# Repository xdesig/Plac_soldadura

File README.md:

#  Plataforma de Soldadura (Control de Temperatura)

> [!NOTE]
> Documentation in Galego 
> [traductor](https://tradutorgaio.xunta.gal/TradutorPublico/traducir/index)

Este repositorio conten o deseno de hardware, esquema e firmware para o desenvolvemento dun **controlador termico intelixente** aplicado a unha placa calefactora de 230Vac. O sistema esta desenado para labores de soldadura e desoldadura de componentes SMD/THD en proxectos persoais, educativos e experimentais.

---

## Versions do Proxecto

O repositorio esta dividido en duas variantes segundo o microcontrolador utilizado:

### 1. [Plataforma_sold_ATmega328p](./Plataforma_sold_ATmega328p)

- **Microcontrolador:** ATmega328P-AU (TQFP-32).
- **Descricion:** Version mais lixeira e eficiente baseada na arquitectura clasica de Arduino. Demostra que non e preciso usar un potente ESP32 para realizar este traballo.
**Caracteristicas:** Control de potencia, visualizacion en pantalla OLED 128x64 (SSD1306) e illamento galvanico.

**[Ver documentacion e BOM do ATmega328P](./Plataforma_sold_ATmega328p)**

---

### 2. [Plataforma_sold_ESP32-C3](./Plataforma_sold_ESP32-C3)

**Microcontrolador:** ESP32-C3 SuperMini (RISC-V).
**Descricion:** Version baseada no chip ESP32-C3, aproveitando a sua maior velocidade de procesamento e conectividade.
**Caracteristicas:** Interface OLED I2C, control mediante encoder rotatorio e procesamento mais rapido da curva de temperatura.

**[Ver documentacion e BOM do ESP32-C3](./Plataforma_sold_ESP32-C3)**

---

##  Caracteristicas Xerais

Ambas versions comparten a seguinte arquitectura e funcionalidade basica:

- **Control Termico:** Axuste preciso da temperatura e control de potencia do elemento calefactor.
- **Seguridade:** Deteccion de fallos no termistor e corte de emerxencia por sobrequecemento (300 C).
- **Aisllamento:** Illamento galvanico mediante micro-fonte de alimentacion conmutada integrada na PCB.
- **Etapa de Potencia:** Control de carga AC a 230Vac mediante SSR / Triac (BTA06-400B e optoacoplador MOC3041).
- **Interface:** Pantalla OLED SSD1306 (128x64 px) e selector mediante encoder rotatorio e pulsador.

---

## Estrutura do Repositorio

* `Plataforma_sold_ATmega328p/`: Proxecto, PCB e BOM para ATmega328P
* `Plataforma_sold_ESP32-C3/`: Proxecto, PCB e BOM para ESP32-C3
* `README.md`: Descricion xeral do repositorio

---

Saúdos.

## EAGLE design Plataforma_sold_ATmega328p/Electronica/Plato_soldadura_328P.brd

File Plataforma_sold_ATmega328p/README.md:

# Controlador de placa para soldar Con ATmega328p

> [!NOTE]
> Documentation in Galego 
> [traductor](https://tradutorgaio.xunta.gal/TradutorPublico/traducir/index)

Tr&aacute;tase dun **controlador t&eacute;rmico intelixente** de placa calefactora 230Vac para soldar/desoldar, dese&ntilde;ado para uso persoal, educativo e experimental. Baseado en ATmega328, non &eacute; preciso usar un potente ESP32 para realizar este traballo, e permite:

- Axuste preciso da temperatura (ata 300&deg;C).
- Control "PID" simple e estable.
- Detecci&oacute;n de fallos do termistor.
- Gr&aacute;fico en tempo real da temperatura.
- Indicador ON/OFF e potencia aplicada ao calefactor na pantalla.
- Corte de emerxencia por sobrequecemento (300&deg;C).
- Illamento galv&aacute;nico (micro-fonte de alimentaci&oacute;n conmutada).
- Control mediante SSR (Triac) a 230Vac.

<br>
---

## [Versi&oacute;n 00]

## Listado de Compoñentes (BOM)

|Cant | Valor        | Dispositivo                       | Parte            | Descrición         |
|-----|--------------|-----------------------------------|------------------|------------------|
| **1** | 100R | R0603 | `R1` | Resistor |
| **1** | 100nF | C0603 | `C3` | Capacitor |
| **3** | 10K | R0603 | `R6`, `R8`, `R9` | Resistor |
| **1** | 10nF / 400V | C075-042X103 | `C1` | Capacitor (400V) |
| **1** | 10uF | C1206 | `C2` | Capacitor |
| **1** | 1K | R0603 | `R7` | Resistor |
| **1** | 1uF | C0603 | `C4` | Capacitor |
| **4** | 200R | R1206 | `R2`, `R3`, `R12`, `R13` | Resistor |
| **1** | 22-05-7028-02 | 7395-02 | `J1` | Connector |
| **1** | 39R | 0204/7 | `R4` | Resistor |
| **1** | 47K | R0603 | `R5` | Resistor |
| **2** | 4K7 | R0603 | `R10`, `R11` | Resistor |
| **1** | ATMEGA328P-AU | TQFP-32 | `IC3` | 8-bit Microcontrolador 32KB Flash |
| **1** | B3U-1000P | SMD_157SW | `S6` | Pulsador 4x3mm SMD H2.5mm |
| **1** | BTA06-400B (BT136) | TO-220AB | `T1` | Triac  |
| **1** | CSTCE16M0V53C-R0 | Resonador | `Y1` | Resonador 16MHz SMD |
| **1** | OLED 0.96" I2C | 128x64 Modulo | `OL1` | SSD1306 [GND, VCC, SCL, SDA] |
| **1** | Fusible| TE5 | `F1` | Fusible |
| **1** | MOC3041 | DIL06 / DIP-6 | `OK1` | Optoacoplador, Triac |
| **1** | Rotary Encoder | Rotary Enc Plain | `SW2` | Encoder rotativo pulsador |
| **1** | RPDZN5W6H | Module | `U1` | Modulo Micro fuente A. |

## Deseñado en Entrimo con agarimo.

### Author and license
* Author: XDeSIG [No Twitter, no X]
* License:[ CERN Open Hardware Licence Version 2 - S - Reciprocal][CERN-OHL-W]
* Certification:[ Open Hardware Certification: ES000057][OSHWA]

<br>

Sa&uacute;dos.
---
[ROTARTY_ENCODER]: https://github.com/xdesig/Plac_soldadura/blob/main/Imaxes/Rotary_encoder.webp
[RPDZN5W6H]: https://github.com/xdesig/Plac_soldadura/blob/main/Imaxes/ac-dc_5V700mA.png
[CERN-OHL-W]: https://ohwr.org/cern_ohl_w_v2.pdf
[OSHWA]: https://certification.oshwa.org/list.html

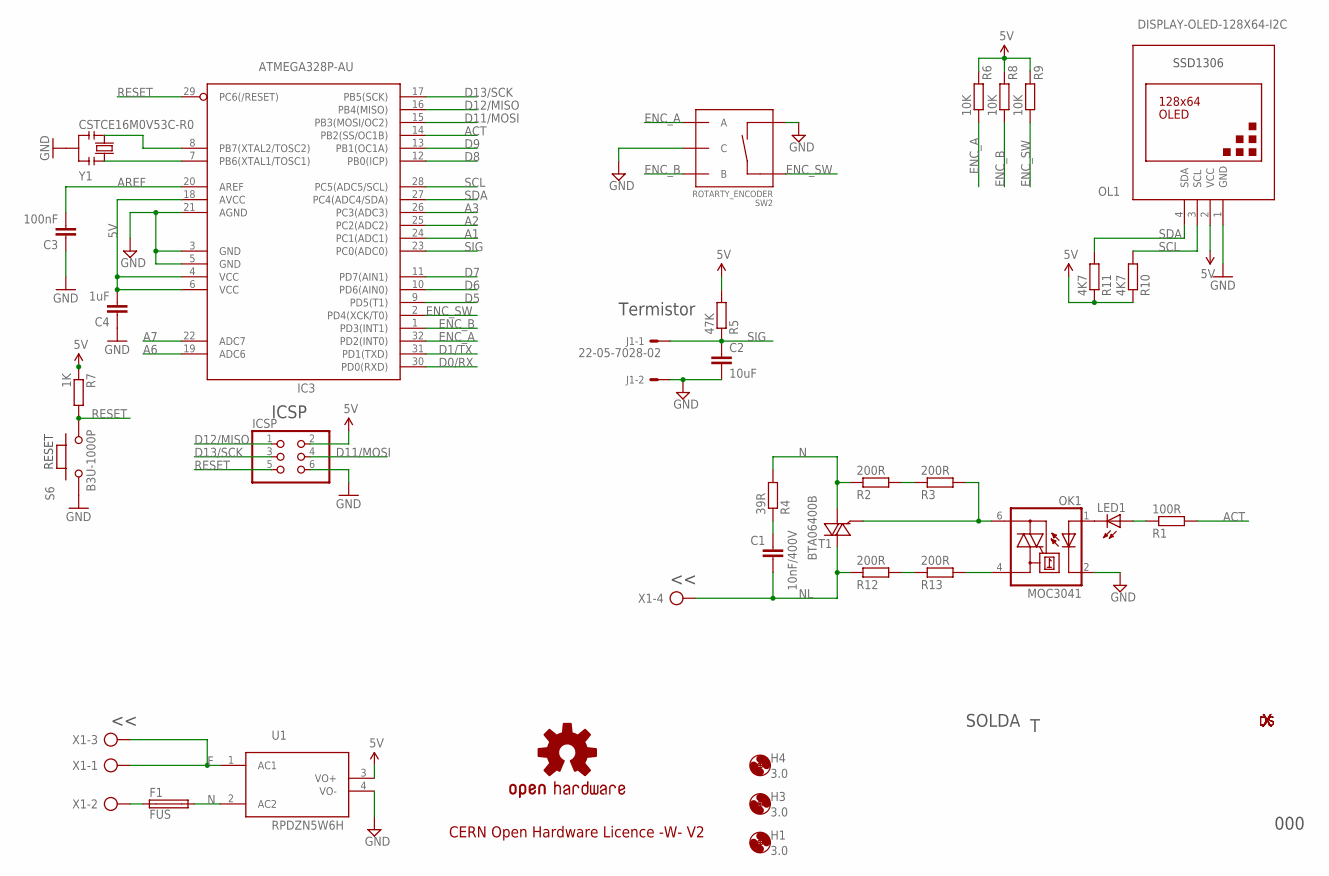
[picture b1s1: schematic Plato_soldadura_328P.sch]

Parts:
C1: 10nF/400V; C075-042X103
C2: 10uF; C1206
C3: 100nF; C0603
C4: 1uF; C0603
F1: FUS; TE5
H1, H3, H4: 3.0; 3,0
IC3: ATMEGA328P-AU; TQFP32-08
ICSP: 0114_PH254-203DF118A00V; 2X03
J1: 22-05-7028-02; 7395-02
LED1: LEDCHIP-LED0603; CHIP-LED0603
LOGO2: OSHW-LOGOL; ESCORNA_LBRESCORNA_CPU_2_10_SPARKFUN-AESTHETICS_OSHW-LOGO-L
OK1: MOC3041; DIL06
OL1: DISPLAY-OLED-128X64-I2C
R1: 100R; R0603
R2, R3, R12, R13: 200R; R1206
R4: 39R; 0204/7
R5: 47K; R0603
R6, R8, R9: 10K; R0603
R7: 1K; R0603
R10, R11: 4K7; R0603
S6: B3U-1000P; SMD_157SW
SW2: ROTARTY_ENCODER; ROTARY_ENC_PLAIN
T1: BTA06400B; TO220AB
U1: RPDZN5W6H
U$7: XDESIG_XDESIG5MM; XDESIG_XDESIG_CU
U$8: XDESIG_XDESIG21; XDESIG_XDESIG
X1: AK500/4-H
Y1: CSTCE16M0V53C-R0; RESONATOR

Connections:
5V: C4.2, IC3.4 (VCC), IC3.6 (VCC), IC3.18 (AVCC), ICSP.2, OL1.2 (VCC), R5.2, R6.2, R7.1, R8.2, R9.2, R10.1, R11.1, U1.3 (VO+)
A1: IC3.24 (PC1(ADC1))
A2: IC3.25 (PC2(ADC2))
A3: IC3.26 (PC3(ADC3))
A6: IC3.19 (ADC6)
A7: IC3.22 (ADC7)
ACT: IC3.14 (PB2(SS/OC1B)), R1.2
AREF: C3.2, IC3.20 (AREF)
D0/RX: IC3.30 (PD0(RXD))
D1/TX: IC3.31 (PD1(TXD))
D5: IC3.9 (PD5(T1))
D6: IC3.10 (PD6(AIN0))
D7: IC3.11 (PD7(AIN1))
D8: IC3.12 (PB0(ICP))
D9: IC3.13 (PB1(OC1A))
D11/MOSI: IC3.15 (PB3(MOSI/OC2)), ICSP.4
D12/MISO: IC3.16 (PB4(MISO)), ICSP.1
D13/SCK: IC3.17 (PB5(SCK)), ICSP.3
ENC_A: IC3.32 (PD2(INT0)), R6.1, SW2.A
ENC_B: IC3.1 (PD3(INT1)), R8.1, SW2.B
ENC_SW: IC3.2 (PD4(XCK/T0)), R9.1, SW2.SW+
F: U1.1 (AC1), X1.1, X1.3
GND: C2.2, C3.1, C4.1, IC3.3 (GND), IC3.5 (GND), IC3.21 (AGND), ICSP.6, J1.2, OK1.2 (C), OL1.1 (GND), S6.1, SW2.C, SW2.SW-, U1.4 (VO-), Y1.2
N: F1.2, R2.1, R4.2, T1.1 (A1), U1.2 (AC2)
unnamed: OK1.4 (A1), R13.2
unnamed: F1.1, X1.2
unnamed: OK1.6 (A2), R3.2, T1.3 (G)
unnamed: LED1.C, OK1.1 (A)
unnamed: LED1.A, R1.1
unnamed: R2.2, R3.1
unnamed: R12.2, R13.1
unnamed: C1.1, R4.1
unnamed: IC3.7 (PB6(XTAL1/TOSC1)), Y1.1
unnamed: IC3.8 (PB7(XTAL2/TOSC2)), Y1.3
NL: C1.2, R12.1, T1.2 (A2), X1.4
RESET: IC3.29 (PC6(/RESET)), ICSP.5, R7.2, S6.2
SCL: IC3.28 (PC5(ADC5/SCL)), OL1.3 (SCL), R10.2
SDA: IC3.27 (PC4(ADC4/SDA)), OL1.4 (SDA), R11.2
SIG: C2.1, IC3.23 (PC0(ADC0)), J1.1, R5.1

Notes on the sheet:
CERN Open Hardware Licence -W- V2
ICSP
RESET
Termistor
SOLDA
SSD1306
000

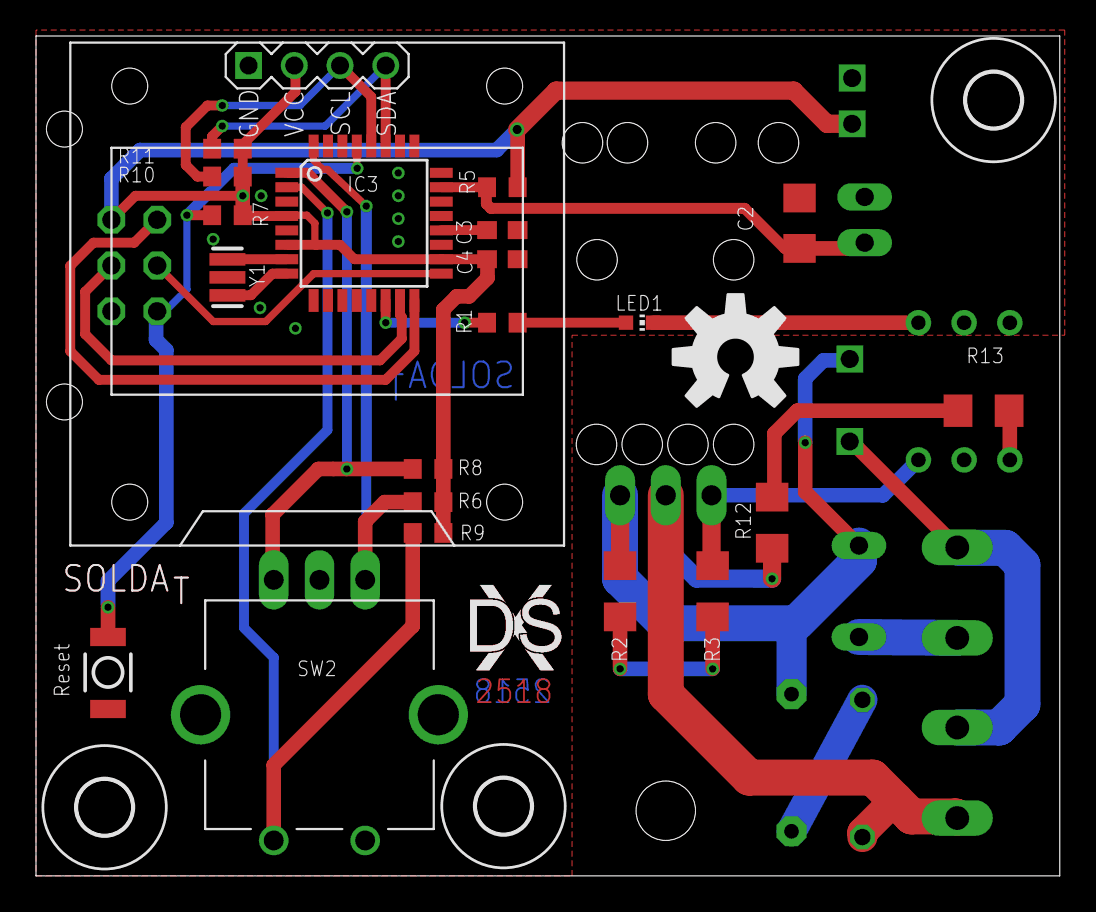
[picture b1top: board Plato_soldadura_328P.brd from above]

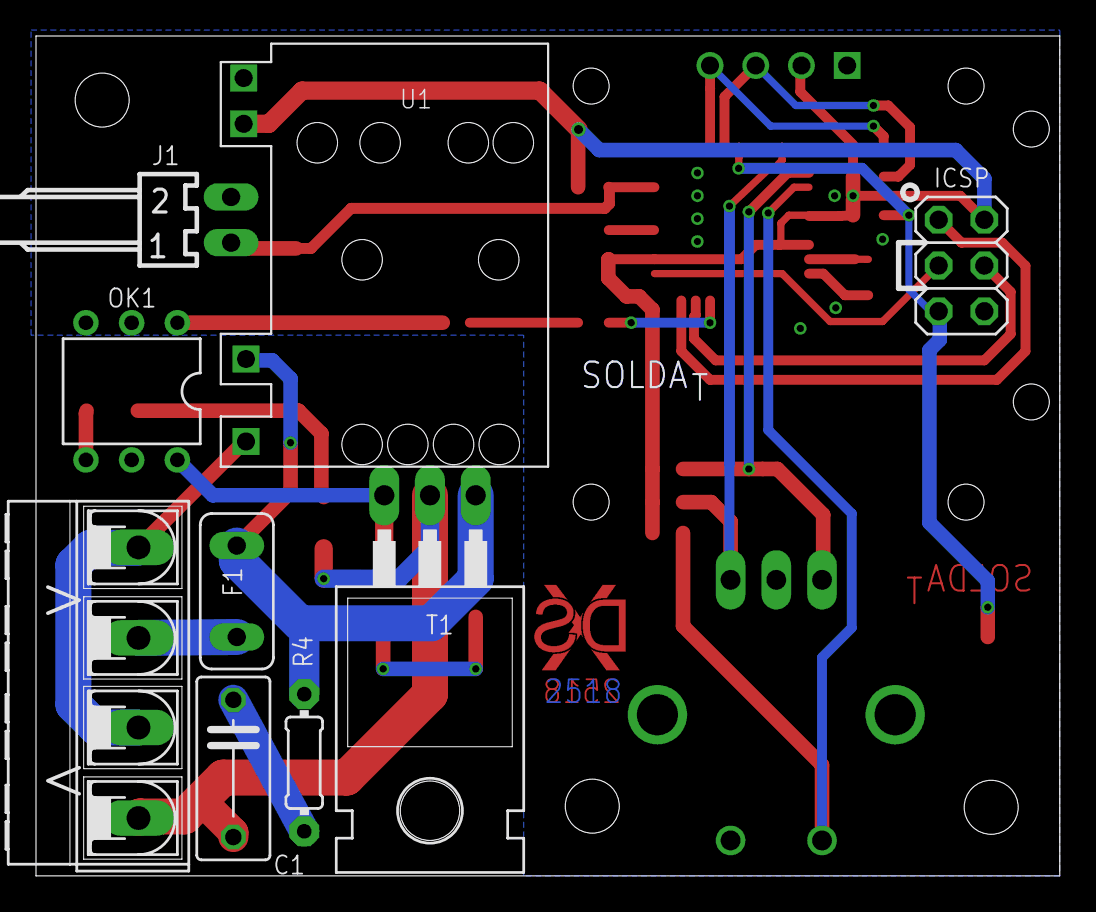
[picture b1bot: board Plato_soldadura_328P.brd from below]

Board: 2 copper layers, 56.9 x 46.7 mm, 36 parts (9 on the bottom side), 27 nets.

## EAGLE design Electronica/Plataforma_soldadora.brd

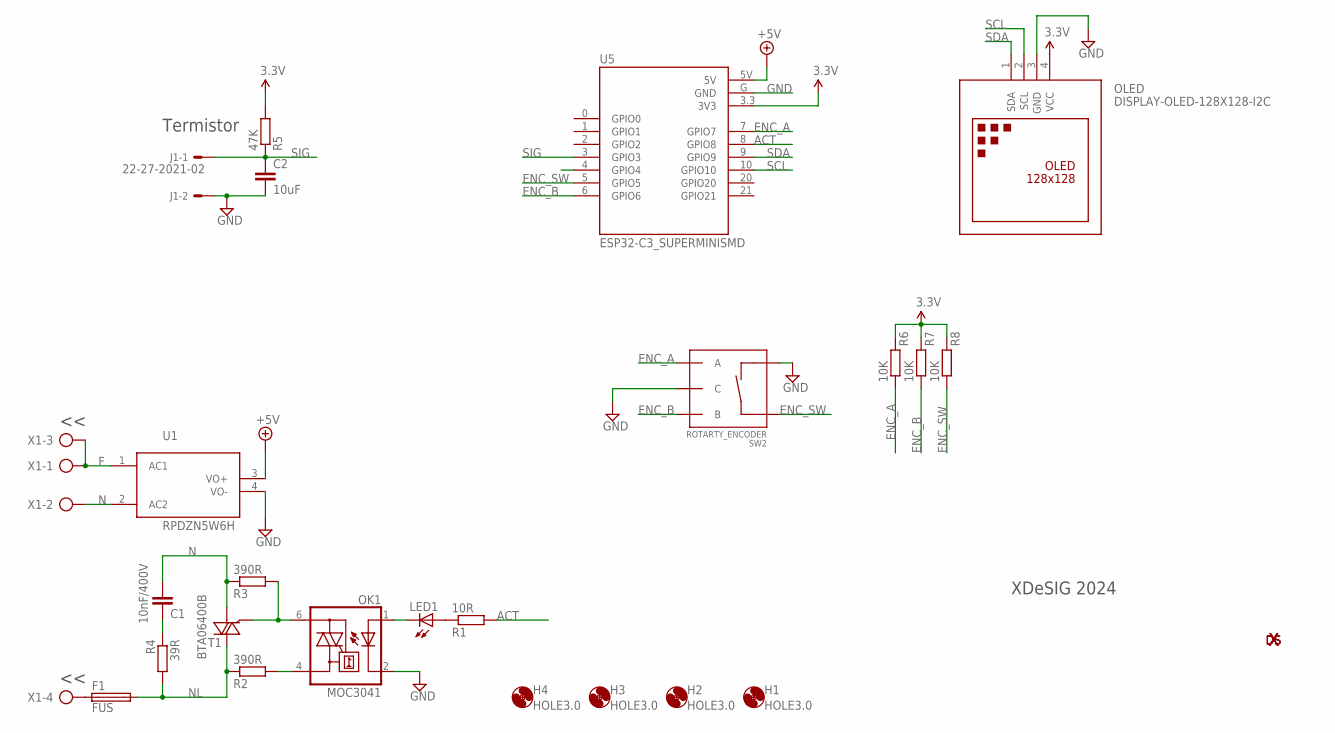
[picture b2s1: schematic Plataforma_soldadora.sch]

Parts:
C1: 10nF/400V; C075-042X103
C2: 10uF; C1206K
F1: FUS; TE5
H1, H2, H3, H4: HOLE3.0; HOLES_3,0
J1: 22-27-2021-02; 6410-02
LED1: LED3MM
OK1: MOC3041; DIL06
OLED: DISPLAY-OLED-128X128-I2C
R1: 10R; R0603
R2, R3: 390R; 0204/7
R4: 39R; 0204/7
R5: 47K; R0603
R6, R7, R8: 10K; R0603
SW2: ROTARTY_ENCODER; ROTARY_ENC_PLAIN
T1: BTA06400B; TO220AB
U1: RPDZN5W6H
U5: ESP32-C3_SUPERMINISMD; MODULE_ESP-C3_SUPERMINI_SMD
U$2: XDESIG_XDESIG5MM; XDESIG_XDESIG_CU
U$3: XDESIG_XDESIG21; XDESIG_XDESIG
X1: AK500/4-H

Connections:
3.3V: OLED.4 (VCC), R5.2, R6.2, R7.2, R8.2, U5.3.3 (3V3)
+5V: U1.3 (VO+), U5.5V
ACT: R1.2, U5.8 (GPIO8)
ENC_A: R6.1, SW2.A, U5.7 (GPIO7)
ENC_B: R7.1, SW2.B, U5.6 (GPIO6)
ENC_SW: R8.1, SW2.SW+, U5.5 (GPIO5)
F: U1.1 (AC1), X1.1, X1.3
GND: C2.2, J1.2, OK1.2 (C), OLED.3 (GND), SW2.C, SW2.SW-, U1.4 (VO-), U5.G (GND)
N: C1.2, R3.1, T1.1 (A1), U1.2 (AC2), X1.2
unnamed: OK1.4 (A1), R2.2
unnamed: F1.1, X1.4
unnamed: OK1.6 (A2), R3.2, T1.3 (G)
unnamed: LED1.K (C), OK1.1 (A)
unnamed: LED1.A, R1.1
unnamed: C1.1, R4.1
NL: F1.2, R2.1, R4.2, T1.2 (A2)
SCL: OLED.2 (SCL), U5.10 (GPIO10)
SDA: OLED.1 (SDA), U5.9 (GPIO9)
SIG: C2.1, J1.1, R5.1, U5.3 (GPIO3)

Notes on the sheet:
Termistor
XDeSIG 2024

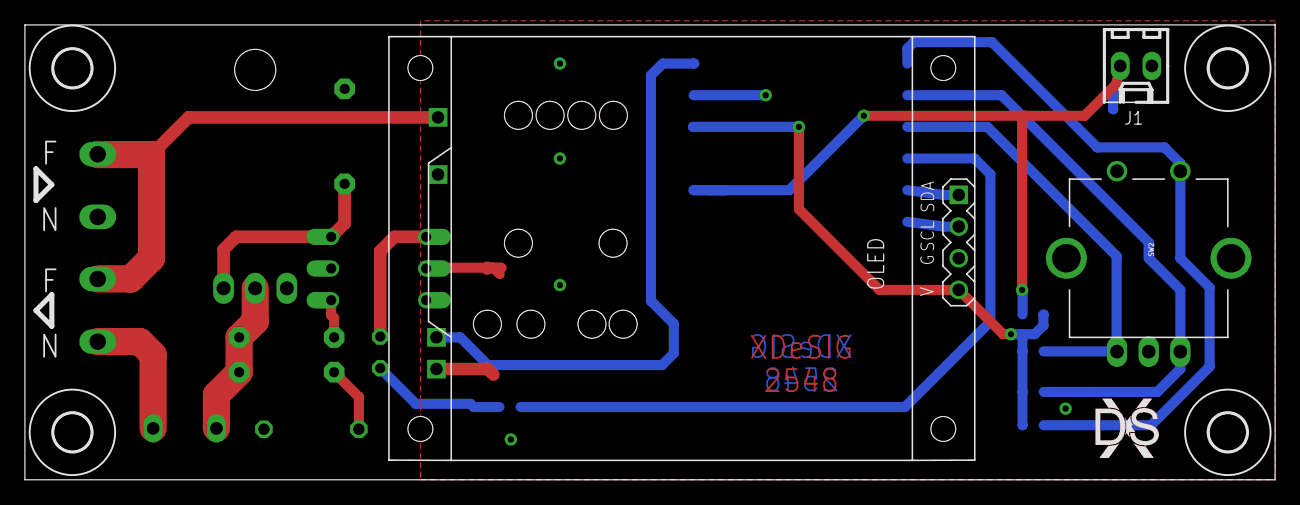
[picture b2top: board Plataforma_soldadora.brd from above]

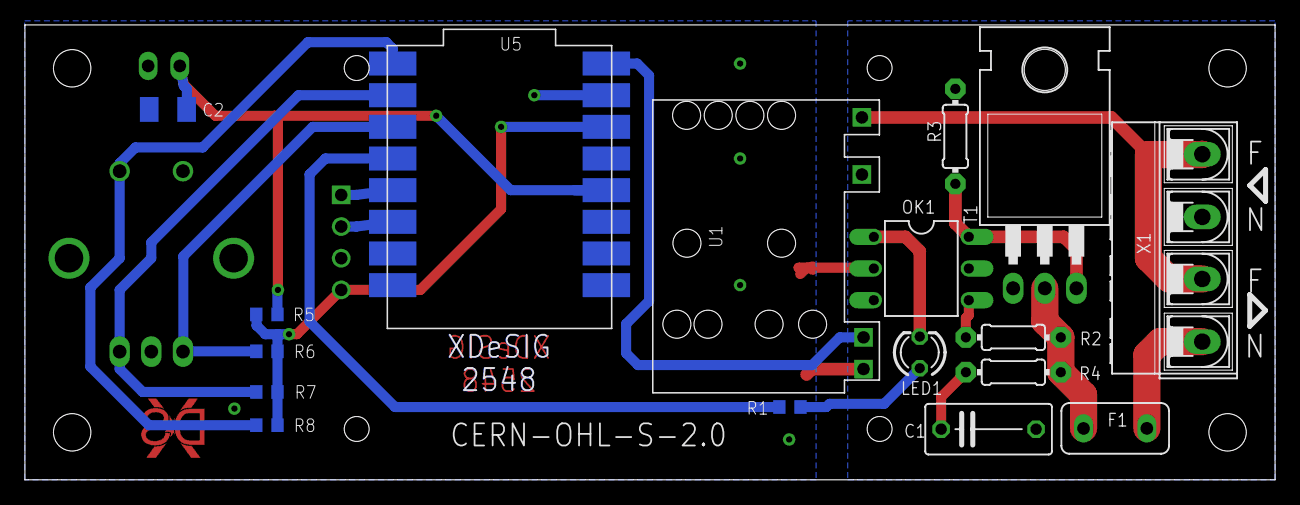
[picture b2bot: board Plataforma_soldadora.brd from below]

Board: 2 copper layers, 100.3 x 36.5 mm, 26 parts (17 on the bottom side), 19 nets.

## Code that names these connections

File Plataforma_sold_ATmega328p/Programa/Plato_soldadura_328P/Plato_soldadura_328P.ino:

#include <Arduino.h>
#include <U8g2lib.h>
#include <PID_v1.h>
#include <Encoder.h>

// --- PINS SEGUNDO O TEU ESQUEMA ---
#define PIN_TRIAC 13
#define PIN_NTC A3//A0
#define PIN_ENC_A 2
#define PIN_ENC_B 3
#define PIN_ENC_SW 4

// --- LÍMITES DE SEGURIDADE ---
#define TEMP_MAX_SEGURA 325.0
#define SENSOR_MIN 5    // Curto
#define SENSOR_MAX 1018 // Aberto

U8G2_SSD1306_128X64_NONAME_1_HW_I2C u8g2(U8G2_R0, /* reset=*/ U8X8_PIN_NONE);
Encoder myEnc(PIN_ENC_A, PIN_ENC_B);

double setpoint = 200; // Temperatura inicial axustada a 200C
double input = 0, output = 0;
bool sistemaActivo = false;
bool erroCritico = false;

// PID: Kp, Ki, Kd (Valores base para plancha térmica)
double Kp=2, Ki=0.5, Kd=2;
PID myPID(&input, &output, &setpoint, Kp, Ki, Kd, DIRECT);

float lerTemperatura() {
  int raw = analogRead(PIN_NTC);
  if (raw < SENSOR_MIN || raw > SENSOR_MAX) { erroCritico = true; return 999.0; }
  
  float resistencia = 47000.0 / (1023.0 / (float)raw - 1.0);
  float temp = 1 / (1 / (273.15 + 25) + log(resistencia / 100000.0) / 3950.0);
  float celsius = temp - 273.15;
  if (celsius > TEMP_MAX_SEGURA) erroCritico = true;
  return celsius;
}

void setup() {
  pinMode(PIN_TRIAC, OUTPUT);
  digitalWrite(PIN_TRIAC, LOW);
  pinMode(PIN_ENC_SW, INPUT_PULLUP);
  u8g2.begin();
  myPID.SetMode(AUTOMATIC);
  myPID.SetOutputLimits(0, 255);
  myPID.SetSampleTime(500); 
}

void loop() {
  input = lerTemperatura();

  // 1. CONTROL DE ENCENDIDO/APAGADO
  if (digitalRead(PIN_ENC_SW) == LOW) {
    delay(300); // Debounce
    sistemaActivo = !sistemaActivo;
    if (sistemaActivo) {
      setpoint = 200; // Reseteamos a 200C ao acender
    } else {
      digitalWrite(PIN_TRIAC, LOW);
      output = 0;
    }
  }

  // 2. LÓXICA DE CONTROL
  if (sistemaActivo && !erroCritico) {
    long steps = myEnc.read() / 4;
    if (steps != 0) {
      setpoint = constrain(setpoint + steps, 0, 300);
      myEnc.write(0);
    }
    myPID.Compute();
    analogWrite(PIN_TRIAC, output);
  } else {
    digitalWrite(PIN_TRIAC, LOW);
  }

  // 3. PANTALLA (MODO PÁXINA PARA BAIXA RAM)
  u8g2.firstPage();
  do {
    if (erroCritico) {
      u8g2.setFont(u8g2_font_9x15_tr);
      u8g2.drawStr(10, 35, "ERRO SENSOR!");
    } else {
      // Temp Actual
      u8g2.setFont(u8g2_font_logisoso32_tf);
      u8g2.setCursor(0, 42);
      u8g2.print((int)input); u8g2.print("C");
      
      // Info PWM á dereita
      u8g2.setFont(u8g2_font_6x12_tr);
      u8g2.setCursor(85, 25); u8g2.print(F("PWR:"));
      u8g2.setCursor(85, 40); u8g2.print(map(output, 0, 255, 0, 100)); u8g2.print(F("%"));

      // Barra e Setpoint
      u8g2.drawFrame(0, 48, 128, 6);
      u8g2.drawBox(0, 48, map(output, 0, 255, 0, 128), 6);
      u8g2.setCursor(0, 62);
      u8g2.print(F("SET: ")); u8g2.print((int)setpoint); u8g2.print(F("C"));
      u8g2.setCursor(95, 62);
      u8g2.print(sistemaActivo ? F("ON") : F("OFF"));
    }
  } while ( u8g2.nextPage() );
}

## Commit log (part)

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2025-11-24 Fix image link format in README.md
2025-11-24 Fix formatting in README.md
2025-11-24 Fix image source and alignment in README
    Updated image source for better visibility and alignment.
2025-11-24 Change emergency cutoff temperature in README
    Updated emergency cutoff temperature from 360°C to 300°C.
2025-11-24 Revise features and author details in README
    Updated features and author information in README.
2025-11-25 Add design credit to README
2025-11-25 Fix formatting and update author section in README
2025-11-25 Correct encoding errors in README.md
    Fix encoding issue in README.md for correct display.

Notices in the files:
Electronica/Plataforma_soldadora.brd:
CERN-OHL-S-2.0
parts and their libraries:
diy-modules: Released under the Creative Commons Attribution 4.0 International License: http://creativecommons.org/licenses/by/4.0
SparkFun-Electromechanical: Licensing: Creative Commons ShareAlike 4.0 International - https://creativecommons.org/licenses/by-sa/4.0
